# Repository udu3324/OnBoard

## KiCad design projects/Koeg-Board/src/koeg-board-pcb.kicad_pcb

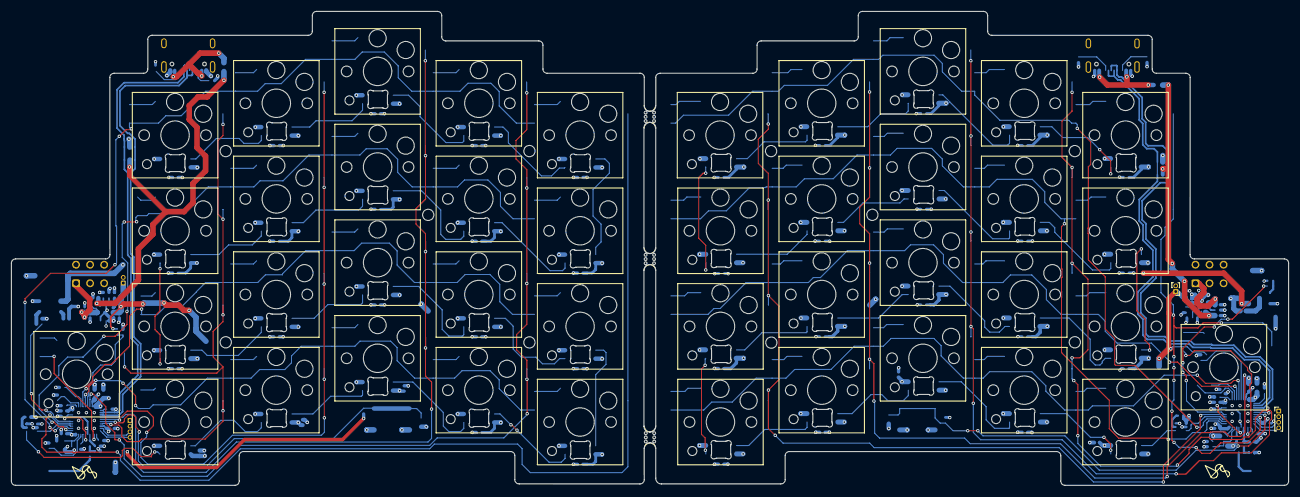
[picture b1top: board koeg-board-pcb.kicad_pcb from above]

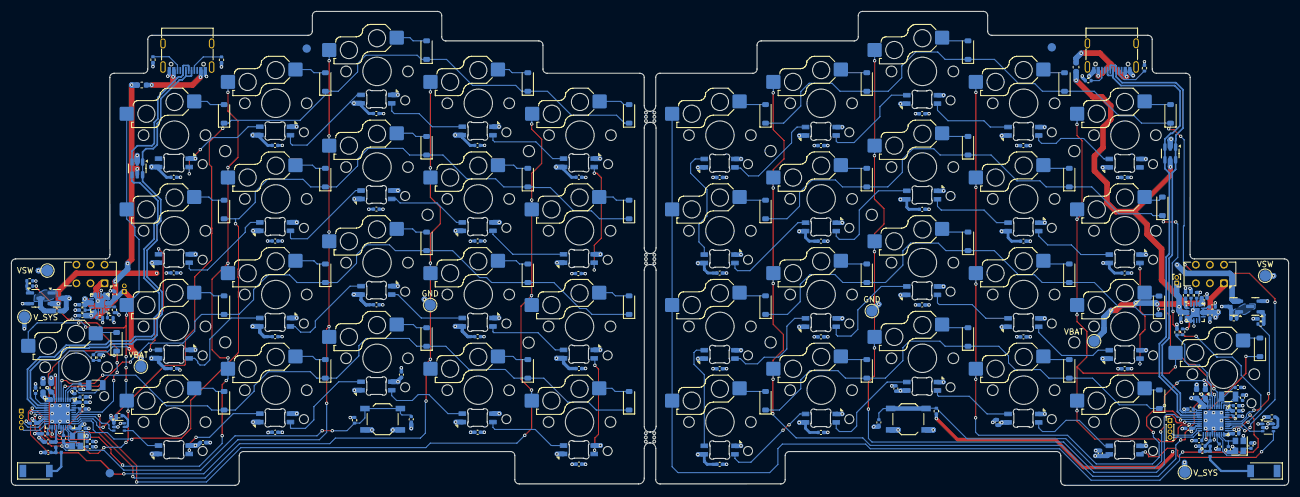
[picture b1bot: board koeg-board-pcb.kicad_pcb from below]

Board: 4 copper layers, 227.1 x 84.3 mm, 290 parts (236 on the bottom side), 175 nets.

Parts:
AE65, AE66: Antenna_Chip; ANTC5020X110N
BO1, BO2, BO3: break off; mouse-bite-2mm-slot
C2, C4, C18, C20, C41, C42, C43, C44, C47, C48, C49, C50, C51, C52, C53, C54, C55, C56, C57, C58, C59, C60, C61, C62, C63, C64, C65, C66, C67, C68, C69, C70, C71, C72, C73, C74, C75, C76, C77, C78, C79, C80, C81, C82, C83, C84, C85, C86: 100nF; C_0402_1005Metric
C5, C21: 100pF; C_0402_1005Metric
C6, C22: 820pF; C_0402_1005Metric
C7, C23, C39, C40: 1uF; C_0402_1005Metric
C9, C25, C87, C88, C89, C90, C91, C92: 4.7uF; C_0402_1005Metric
C10, C19, C24, C26: 4.7uF; C_0603_1608Metric
C11, C12, C15, C16, C27, C28, C31, C32: 12pF; C_0402_1005Metric
C13, C29: 1pF; C_0402_1005Metric
C14, C30: 1.2pF; C_0402_1005Metric
D2, D3, D4, D5, D6, D7, D8, D9, D10, D11, D12, D13, D14, D15, D16, D17, D18, D19, D20, D21, D22, D44, D45, D46, D47, D48, D49, D50, D51, D52, D53, D54, D55, D56, D57, D58, D59, D60, D61, D62, D63, D64: 1N5819; D_SOD-123
D23, D24, D25, D26, D27, D28, D29, D30, D31, D32, D33, D34, D35, D36, D37, D38, D39, D40, D41, D42, D65, D66, D67, D68, D69, D70, D71, D72, D73, D74, D75, D76, D77, D78, D79, D80, D81, D82, D83, D84: SK6812MINI-E; LED_6028R
F1, F2: 500mA; Fuse_0603_1608Metric
FID1, FID2, FID3: Fiducial; Fiducial_1.5mm_Mask3mm
H1, H2, H3, H4, H5, H6, H7, H8, H9, H10: MountingHole; MountingHole_2mm
J1, J4: Conn_01x02; PinHeader_1x02_P1.00mm_Vertical
J2, J5: SWD_Connector; PinHeader_1x04_P1.00mm_Vertical
J3, J6: USB_C_Receptacle_USB2.0_16P; USB_C_Receptacle_G-Switch_GT-USB-7010ASV
L4, L9: 4.7nH; L_0402_1005Metric
L5, L10: 2.2nH; L_0402_1005Metric
LOGO1, LOGO2: Logo_Open_Hardware_Small; BM logo
Q5, Q6: AO3401A; SOT-23
Q7, Q8: 2N7002; SOT-23
R1, R8: 100K; R_0402_1005Metric
R2, R9: 806k; R_0402_1005Metric
R3, R10: 2M; R_0402_1005Metric
R4, R5, R11, R12: 5.1k; R_0402_1005Metric
R6, R7: 100R; R_0402_1005Metric
R13, R14, R16, R18, R20, R22: 10k; R_0402_1005Metric
R27, R28: 3.9k; R_0402_1005Metric
R29, R30, R31, R32, R33, R34: 1.5k; R_0402_1005Metric
SW1, SW24: Reset Button; SW_SPST_TL3342
SW2, SW25: SW_On_Off; SW_CK_JS202011AQN_DPDT_Angled
SW3, SW4, SW5, SW6, SW7, SW8, SW9, SW10, SW11, SW12, SW13, SW14, SW15, SW16, SW17, SW18, SW19, SW20, SW21, SW22, SW26, SW27, SW28, SW29, SW30, SW31, SW32, SW33, SW34, SW35, SW36, SW37, SW38, SW39, SW40, SW41, SW42, SW43, SW44, SW45: SW_Push; SW_Hotswap_Kailh_Choc_V1V2_1.00u
SW23, SW46: SW_Push; SW_Hotswap_Kailh_Choc_V1V2_1.75u_90deg
TP1, TP5: VSW; TestPoint_Pad_D2.0mm
TP2, TP6: V_SYS; TestPoint_Pad_D2.0mm
TP3, TP7: VBAT; TestPoint_Pad_D2.0mm
TP4, TP8: GND; TestPoint_Pad_D2.0mm
U2, U5: USBLC6-2SC6; SOT-23-6
U7, U8: nRF52833_QDxx; QFN-40-1EP_5x5mm_P0.4mm_EP3.6x3.6mm
U9, U10: TXB0101DCK; SOT-363_SC-70-6
U11, U12: BQ24075RGT; VQFN-16-1EP_3x3mm_P0.5mm_EP1.6x1.6mm
Y1, Y2: 32MHz; Crystal_SMD_2520-4Pin_2.5x2.0mm
Y3, Y4: 32.768 kHz; Crystal_SMD_3215-2Pin_3.2x1.5mm

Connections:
/left/ANT: C13.2, L4.1, U7.24 (ANT)
/left/BT_PIN: R2.2, R3.1, U7.6 (P1.09)
/left/CC1: J3.A5 (CC1), R4.1
/left/CC2: J3.B5 (CC2), R5.1
/left/COL0: SW3.2, SW8.2, SW13.2, SW18.2, U7.34 (AIN5/P0.29)
/left/COL1: SW4.2, SW9.2, SW14.2, SW19.2, U7.7 (P0.11)
/left/COL2: SW5.2, SW10.2, SW15.2, SW20.2, U7.14 (P0.15)
/left/COL3: SW6.2, SW11.2, SW16.2, SW21.2, U7.15 (P0.17)
/left/COL4: SW7.2, SW12.2, SW17.2, SW22.2, SW23.2, U7.17 (P0.20)
/left/DEC1: C4.1, U7.1 (DEC1)
/left/DEC3: C5.1, U7.27 (DEC3)
/left/DEC4-6: C7.1, U7.26 (DEC6), U7.38 (DEC4)
/left/DEC5: C6.1, U7.21 (DEC5)
/left/DECUSB: C9.1, U7.11 (DECUSB)
/left/LED_EN: R6.1, U7.35 (AIN6/P0.30)
/left/LED_PIN: U7.33 (AIN4/P0.28), U9.3 (A)
/left/RESET: C2.2, R1.2, SW1.1, U7.16 (P0.18/~RESET)
/left/ROW0: D2.1 (K), D3.1 (K), D4.1 (K), D5.1 (K), D6.1 (K), U7.32 (AIN0/P0.02)
/left/ROW1: D7.1 (K), D8.1 (K), D9.1 (K), D10.1 (K), D11.1 (K), U7.31 (AIN1/P0.03)
/left/ROW2: D12.1 (K), D13.1 (K), D14.1 (K), D15.1 (K), D16.1 (K), U7.4 (AIN2/P0.04)
/left/ROW3: D17.1 (K), D18.1 (K), D19.1 (K), D20.1 (K), D21.1 (K), U7.5 (AIN3/P0.05)
/left/ROW4: D22.1 (K), U7.22 (NFC1/P0.09)
/left/SWDCLK: J2.4, U7.20 (SWDCLK)
/left/SWDIO: J2.3, U7.19 (SWDIO)
/left/USB_D+: J3.A6 (D+), J3.B6 (D+), U2.3 (I/O2), U2.4 (I/O2), U7.13 (D+)
/left/USB_D-: J3.A7 (D-), J3.B7 (D-), U2.1 (I/O1), U2.6 (I/O1), U7.12 (D-)
/left/VBAT: C89.2, J1.1, R2.1, TP3.1, U11.2 (BAT), U11.3 (BAT)
/left/VBUS: C87.2, F1.1, U2.5 (VBUS), U11.13 (IN)
/left/VSW: C19.1, Q5.3 (D), R16.2, SW2.2 (B), TP1.1, U7.9 (VDDH), U7.10 (VBUS), U9.6 (V_{CCB}), U11.6 (EN1)
/left/V_SYS: C10.2, C39.2, C41.2, C43.2, J2.2, R1.1, R20.2, TP2.1, U7.8 (VDD), U7.18 (VDD), U7.30 (VDD), U7.40 (VDD), U9.1 (V_{CCA})
/left/XC1: C11.1, U7.28 (XC1), Y1.1
/left/XC2: C12.1, U7.29 (XC2), Y1.3
/left/XL1: C31.2, U7.2 (XL1/P0.00), Y3.2
/left/XL2: C15.2, U7.3 (XL2/P0.01), Y3.1
/left/leds/DATA: D23.3 (DIN), U9.4 (B)
/left/leds/LED_PWR: C47.2, C49.2, C51.2, C53.2, C55.2, C57.2, C58.2, C59.2, C60.2, C61.2, C67.2, C68.2, C69.2, C70.2, C71.2, C72.2, C73.2, C74.2, C75.2, C76.2, D23.1 (VDD), D24.1 (VDD), D25.1 (VDD), D26.1 (VDD), D27.1 (VDD), D28.1 (VDD), D29.1 (VDD), D30.1 (VDD), D31.1 (VDD), D32.1 (VDD), D33.1 (VDD), D34.1 (VDD), D35.1 (VDD), D36.1 (VDD), D37.1 (VDD), D38.1 (VDD), D39.1 (VDD), D40.1 (VDD), D41.1 (VDD), D42.1 (VDD), Q5.2 (S)
/left/power/ILIM: R29.1, U11.12 (ILIM)
/left/power/ISET: R27.1, U11.16 (ISET)
/left/power/REG-OUT: C91.2, SW2.1 (A), U11.10 (OUT), U11.11 (OUT)
/left/power/TMR: R31.1, U11.14 (TMR)
/left/power/TS: R33.2, U11.1 (TS)
/right/ANT: C29.2, L9.1, U8.24 (ANT)
/right/BT_PIN: R9.2, R10.1, U8.6 (P1.09)
/right/CC1: J6.A5 (CC1), R11.1
/right/CC2: J6.B5 (CC2), R12.1
/right/COL0: SW26.2, SW31.2, SW36.2, SW41.2, U8.34 (AIN5/P0.29)
/right/COL1: SW27.2, SW32.2, SW37.2, SW42.2, U8.7 (P0.11)
/right/COL2: SW28.2, SW33.2, SW38.2, SW43.2, U8.14 (P0.15)
/right/COL3: SW29.2, SW34.2, SW39.2, SW44.2, U8.15 (P0.17)
/right/COL4: SW30.2, SW35.2, SW40.2, SW45.2, SW46.2, U8.17 (P0.20)
/right/DEC1: C20.1, U8.1 (DEC1)
/right/DEC3: C21.1, U8.27 (DEC3)
/right/DEC4-6: C23.1, U8.26 (DEC6), U8.38 (DEC4)
/right/DEC5: C22.1, U8.21 (DEC5)
/right/DECUSB: C25.1, U8.11 (DECUSB)
/right/LED_EN: R7.1, U8.35 (AIN6/P0.30)
/right/LED_PIN: U8.33 (AIN4/P0.28), U10.3 (A)
/right/RESET: C18.2, R8.2, SW24.1, U8.16 (P0.18/~RESET)
/right/ROW0: D44.1 (K), D45.1 (K), D46.1 (K), D47.1 (K), D48.1 (K), U8.32 (AIN0/P0.02)
/right/ROW1: D49.1 (K), D50.1 (K), D51.1 (K), D52.1 (K), D53.1 (K), U8.31 (AIN1/P0.03)
/right/ROW2: D54.1 (K), D55.1 (K), D56.1 (K), D57.1 (K), D58.1 (K), U8.4 (AIN2/P0.04)
/right/ROW3: D59.1 (K), D60.1 (K), D61.1 (K), D62.1 (K), D63.1 (K), U8.5 (AIN3/P0.05)
/right/ROW4: D64.1 (K), U8.22 (NFC1/P0.09)
/right/SWDCLK: J5.4, U8.20 (SWDCLK)
/right/SWDIO: J5.3, U8.19 (SWDIO)
/right/USB_D+: J6.A6 (D+), J6.B6 (D+), U5.3 (I/O2), U5.4 (I/O2), U8.13 (D+)
/right/USB_D-: J6.A7 (D-), J6.B7 (D-), U5.1 (I/O1), U5.6 (I/O1), U8.12 (D-)
/right/VBAT: C90.2, J4.1, R9.1, TP7.1, U12.2 (BAT), U12.3 (BAT)
/right/VBUS: C88.2, F2.1, U5.5 (VBUS), U12.13 (IN)
/right/VSW: C24.1, Q6.3 (D), R18.2, SW25.2 (B), TP5.1, U8.9 (VDDH), U8.10 (VBUS), U10.6 (V_{CCB}), U12.6 (EN1)
/right/V_SYS: C26.2, C40.2, C42.2, C44.2, J5.2, R8.1, R22.2, TP6.1, U8.8 (VDD), U8.18 (VDD), U8.30 (VDD), U8.40 (VDD), U10.1 (V_{CCA})
/right/XC1: C27.1, U8.28 (XC1), Y2.1
/right/XC2: C28.1, U8.29 (XC2), Y2.3
/right/XL1: C32.2, U8.2 (XL1/P0.00), Y4.2
/right/XL2: C16.2, U8.3 (XL2/P0.01), Y4.1
/right/leds/DATA: D65.3 (DIN), U10.4 (B)
/right/leds/LED_PWR: C48.2, C50.2, C52.2, C54.2, C56.2, C62.2, C63.2, C64.2, C65.2, C66.2, C77.2, C78.2, C79.2, C80.2, C81.2, C82.2, C83.2, C84.2, C85.2, C86.2, D65.1 (VDD), D66.1 (VDD), D67.1 (VDD), D68.1 (VDD), D69.1 (VDD), D70.1 (VDD), D71.1 (VDD), D72.1 (VDD), D73.1 (VDD), D74.1 (VDD), D75.1 (VDD), D76.1 (VDD), D77.1 (VDD), D78.1 (VDD), D79.1 (VDD), D80.1 (VDD), D81.1 (VDD), D82.1 (VDD), D83.1 (VDD), D84.1 (VDD), Q6.2 (S)
/right/power/ILIM: R30.1, U12.12 (ILIM)
/right/power/ISET: R28.1, U12.16 (ISET)
/right/power/REG-OUT: C92.2, SW25.1 (A), U12.10 (OUT), U12.11 (OUT)
/right/power/TMR: R32.1, U12.14 (TMR)
/right/power/TS: R34.2, U12.1 (TS)
GND: C2.1, C4.2, C5.2, C6.2, C7.2, C9.2, C10.1, C11.2, C12.2, C13.1, C14.2, C15.1, C16.1, C18.1, C19.2, C20.2, C21.2, C22.2, C23.2, C24.2, C25.2, C26.1, C27.2, C28.2, C29.1, C30.2, C31.1, C32.1, C39.1, C40.1, C41.1, C42.1, C43.1, C44.1, C47.1, C48.1, C49.1, C50.1, C51.1, C52.1, C53.1, C54.1, C55.1, C56.1, C57.1, C58.1, C59.1, C60.1, C61.1, C62.1, C63.1, C64.1, C65.1, C66.1, C67.1, C68.1, C69.1, C70.1, C71.1, C72.1, C73.1, C74.1, C75.1, C76.1, C77.1, C78.1, C79.1, C80.1, C81.1, C82.1, C83.1, C84.1, C85.1, C86.1, C87.1, C88.1, C89.1, C90.1, C91.1, C92.1, D23.4 (VSS), D24.4 (VSS), D25.4 (VSS), D26.4 (VSS), D27.4 (VSS), D28.4 (VSS), D29.4 (VSS), D30.4 (VSS), D31.4 (VSS), D32.4 (VSS), D33.4 (VSS), D34.4 (VSS), D35.4 (VSS), D36.4 (VSS), D37.4 (VSS), D38.4 (VSS), D39.4 (VSS), D40.4 (VSS), D41.4 (VSS), D42.4 (VSS), D65.4 (VSS), D66.4 (VSS), D67.4 (VSS), D68.4 (VSS), D69.4 (VSS), D70.4 (VSS), D71.4 (VSS), D72.4 (VSS), D73.4 (VSS), D74.4 (VSS), D75.4 (VSS), D76.4 (VSS), D77.4 (VSS), D78.4 (VSS), D79.4 (VSS), D80.4 (VSS), D81.4 (VSS), D82.4 (VSS), D83.4 (VSS), D84.4 (VSS), J1.2, J2.1, J3.A1 (GND), J3.A12 (GND), J3.B1 (GND), J3.B12 (GND), J4.2, J5.1, J6.A1 (GND), J6.A12 (GND), J6.B1 (GND), J6.B12 (GND), Q7.2 (S), Q8.2 (S), R3.2, R4.2, R5.2, R10.2, R11.2, R12.2, R13.1, R14.1, R27.2, R28.2, R29.2, R30.2, R31.2, R32.2, R33.1, R34.1, SW1.2, SW24.2, TP4.1, TP8.1, U2.2 (GND), U5.2 (GND), U7.25 (VSS_PA), U7.37 (VSS), U7.41 (VSS), U8.25 (VSS_PA), U8.37 (VSS), U8.41 (VSS), U9.2 (GND), U10.2 (GND), U11.4 (~CE), U11.5 (EN2), U11.8 (VSS), U11.15 (SYSOFF), U11.17 (VSS), U12.4 (~CE), U12.5 (EN2), U12.8 (VSS), U12.15 (SYSOFF), U12.17 (VSS), Y1.2, Y1.4, Y2.2, Y2.4
unnamed: AE65.2 (PCB_Trace), L5.2
unnamed: AE66.2 (PCB_Trace), L10.2
unnamed: C14.1, L4.2, L5.1
unnamed: C30.1, L9.2, L10.1
unnamed: D2.2 (A), SW3.1
unnamed: D3.2 (A), SW4.1
unnamed: D4.2 (A), SW5.1
unnamed: D5.2 (A), SW6.1
unnamed: D6.2 (A), SW7.1
unnamed: D7.2 (A), SW8.1
unnamed: D8.2 (A), SW9.1
unnamed: D9.2 (A), SW10.1
unnamed: D10.2 (A), SW11.1
unnamed: D11.2 (A), SW12.1
unnamed: D12.2 (A), SW13.1
unnamed: D13.2 (A), SW14.1
unnamed: D14.2 (A), SW15.1
unnamed: D15.2 (A), SW16.1
unnamed: D16.2 (A), SW17.1
unnamed: D17.2 (A), SW18.1
unnamed: D18.2 (A), SW19.1
unnamed: D19.2 (A), SW20.1
unnamed: D20.2 (A), SW21.1
unnamed: D21.2 (A), SW22.1
unnamed: D22.2 (A), SW23.1
unnamed: D23.2 (DOUT), D24.3 (DIN)
unnamed: D24.2 (DOUT), D25.3 (DIN)
unnamed: D25.2 (DOUT), D26.3 (DIN)
unnamed: D26.2 (DOUT), D27.3 (DIN)
unnamed: D27.2 (DOUT), D32.3 (DIN)
unnamed: D28.3 (DIN), D29.2 (DOUT)
unnamed: D28.2 (DOUT), D33.3 (DIN)
unnamed: D29.3 (DIN), D30.2 (DOUT)
unnamed: D30.3 (DIN), D31.2 (DOUT)
unnamed: D31.3 (DIN), D32.2 (DOUT)
unnamed: D33.2 (DOUT), D34.3 (DIN)
unnamed: D34.2 (DOUT), D35.3 (DIN)
unnamed: D35.2 (DOUT), D36.3 (DIN)
unnamed: D36.2 (DOUT), D37.3 (DIN)
unnamed: D37.2 (DOUT), D42.3 (DIN)
unnamed: D38.3 (DIN), D39.2 (DOUT)
unnamed: D39.3 (DIN), D40.2 (DOUT)
unnamed: D40.3 (DIN), D41.2 (DOUT)
unnamed: D41.3 (DIN), D42.2 (DOUT)
unnamed: D44.2 (A), SW26.1
unnamed: D45.2 (A), SW27.1
unnamed: D46.2 (A), SW28.1
unnamed: D47.2 (A), SW29.1
unnamed: D48.2 (A), SW30.1
unnamed: D49.2 (A), SW31.1
unnamed: D50.2 (A), SW32.1
unnamed: D51.2 (A), SW33.1
unnamed: D52.2 (A), SW34.1
unnamed: D53.2 (A), SW35.1
unnamed: D54.2 (A), SW36.1
unnamed: D55.2 (A), SW37.1
unnamed: D56.2 (A), SW38.1
unnamed: D57.2 (A), SW39.1
unnamed: D58.2 (A), SW40.1
unnamed: D59.2 (A), SW41.1
unnamed: D60.2 (A), SW42.1
unnamed: D61.2 (A), SW43.1
unnamed: D62.2 (A), SW44.1
unnamed: D63.2 (A), SW45.1
unnamed: D64.2 (A), SW46.1
unnamed: D65.2 (DOUT), D66.3 (DIN)
unnamed: D66.2 (DOUT), D67.3 (DIN)
unnamed: D67.2 (DOUT), D68.3 (DIN)
unnamed: D68.2 (DOUT), D69.3 (DIN)
unnamed: D69.2 (DOUT), D74.3 (DIN)
unnamed: D70.3 (DIN), D71.2 (DOUT)
unnamed: D70.2 (DOUT), D75.3 (DIN)
unnamed: D71.3 (DIN), D72.2 (DOUT)
unnamed: D72.3 (DIN), D73.2 (DOUT)
unnamed: D73.3 (DIN), D74.2 (DOUT)
unnamed: D75.2 (DOUT), D76.3 (DIN)
unnamed: D76.2 (DOUT), D77.3 (DIN)
unnamed: D77.2 (DOUT), D78.3 (DIN)
unnamed: D78.2 (DOUT), D79.3 (DIN)
unnamed: D79.2 (DOUT), D84.3 (DIN)
unnamed: D80.3 (DIN), D81.2 (DOUT)
unnamed: D81.3 (DIN), D82.2 (DOUT)
unnamed: D82.3 (DIN), D83.2 (DOUT)
unnamed: D83.3 (DIN), D84.2 (DOUT)
unnamed: F1.2, J3.A4 (VBUS), J3.A9 (VBUS), J3.B4 (VBUS), J3.B9 (VBUS)
unnamed: F2.2, J6.A4 (VBUS), J6.A9 (VBUS), J6.B4 (VBUS), J6.B9 (VBUS)
unnamed: Q5.1 (G), Q7.3 (D), R16.1
unnamed: Q6.1 (G), Q8.3 (D), R18.1
unnamed: Q7.1 (G), R6.2, R13.2
unnamed: Q8.1 (G), R7.2, R14.2
unnamed: R20.1, U9.5 (OE)
unnamed: R22.1, U10.5 (OE)

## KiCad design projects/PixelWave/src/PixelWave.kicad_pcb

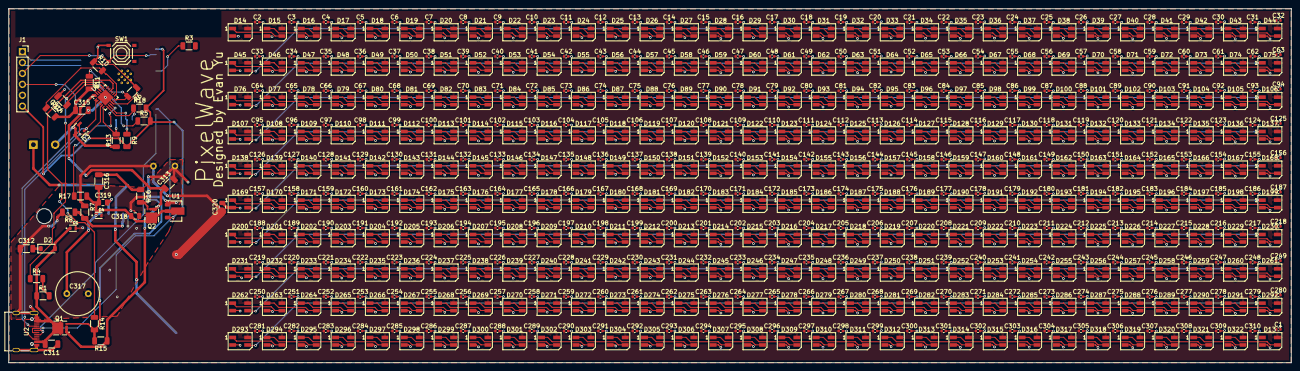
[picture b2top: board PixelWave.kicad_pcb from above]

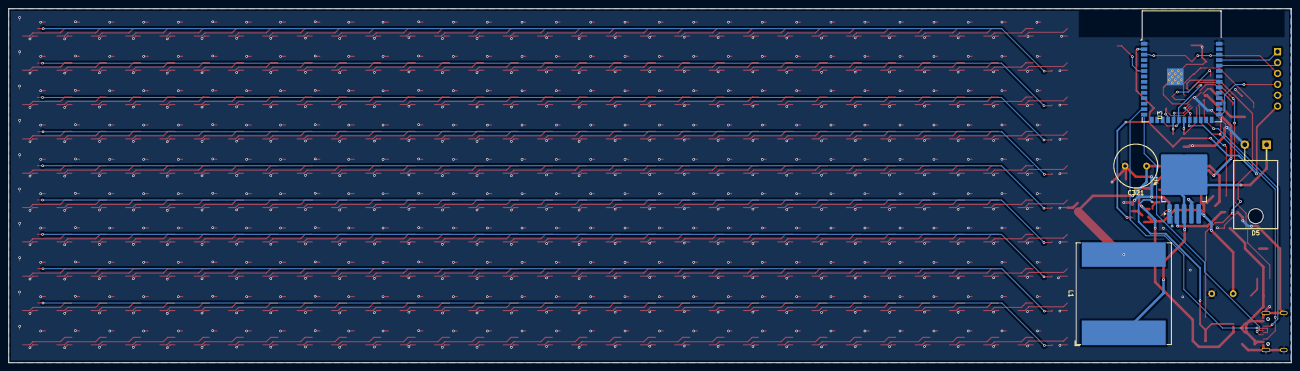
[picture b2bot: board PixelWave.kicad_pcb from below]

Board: 2 copper layers, 298.9 x 82.5 mm, 663 parts (5 on the bottom side), 343 nets.

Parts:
C1, C2, C3, C4, C5, C6, C7, C8, C9, C10, C11, C12, C13, C14, C15, C16, C17, C18, C19, C20, C21, C22, C23, C24, C25, C26, C27, C28, C29, C30, C31, C32, C33, C34, C35, C36, C37, C38, C39, C40, C41, C42, C43, C44, C45, C46, C47, C48, C49, C50, C51, C52, C53, C54, C55, C56, C57, C58, C59, C60, C61, C62, C63, C64, C65, C66, C67, C68, C69, C70, C71, C72, C73, C74, C75, C76, C77, C78, C79, C80, C81, C82, C83, C84, C85, C86, C87, C88, C89, C90, C91, C92, C93, C94, C95, C96, C97, C98, C99, C100, C101, C102, C103, C104, C105, C106, C107, C108, C109, C110, C111, C112, C113, C114, C115, C116, C117, C118, C119, C120, C121, C122, C123, C124, C125, C126, C127, C128, C129, C130, C131, C132, C133, C134, C135, C136, C137, C138, C139, C140, C141, C142, C143, C144, C145, C146, C147, C148, C149, C150, C151, C152, C153, C154, C155, C156, C157, C158, C159, C160, C161, C162, C163, C164, C165, C166, C167, C168, C169, C170, C171, C172, C173, C174, C175, C176, C177, C178, C179, C180, C181, C182, C183, C184, C185, C186, C187, C188, C189, C190, C191, C192, C193, C194, C195, C196, C197, C198, C199, C200, C201, C202, C203, C204, C205, C206, C207, C208, C209, C210, C211, C212, C213, C214, C215, C216, C217, C218, C219, C220, C221, C222, C223, C224, C225, C226, C227, C228, C229, C230, C231, C232, C233, C234, C235, C236, C237, C238, C239, C240, C241, C242, C243, C244, C245, C246, C247, C248, C249, C250, C251, C252, C253, C254, C255, C256, C257, C258, C259, C260, C261, C262, C263, C264, C265, C266, C267, C268, C269, C270, C271, C272, C273, C274, C275, C276, C277, C278, C279, C280, C281, C282, C283, C284, C285, C286, C287, C288, C289, C290, C291, C292, C293, C294, C295, C296, C297, C298, C299, C300, C301, C302, C303, C304, C305, C306, C307, C308, C309, C310: 0.1uF; C_0402_1005Metric
C311: 4.7uF; C_1206_3216Metric
C312, C313, C314, C315: 1uF; C_1206_3216Metric
C316: 100nF; C_1206_3216Metric
C317: 470uF/50V; C_Radial_D10.0mm_H16.0mm_P5.00mm
C318, C319, C320: 1uF; C_0805_2012Metric
C321: 1000uF; C_Radial_D10.0mm_H16.0mm_P5.00mm
D1, D4: ESDA25P35; TVS_ESDA25P35-1U1M
D2: 1N5819W; D_SOD-123
D3: ESDA5V3L; SOT-23-3
D5: MBR1545; TO-220-2_Horizontal_TabDown
D13, D14, D15, D16, D17, D18, D19, D20, D21, D22, D23, D24, D25, D26, D27, D28, D29, D30, D31, D32, D33, D34, D35, D36, D37, D38, D39, D40, D41, D42, D43, D44, D45, D46, D47, D48, D49, D50, D51, D52, D53, D54, D55, D56, D57, D58, D59, D60, D61, D62, D63, D64, D65, D66, D67, D68, D69, D70, D71, D72, D73, D74, D75, D76, D77, D78, D79, D80, D81, D82, D83, D84, D85, D86, D87, D88, D89, D90, D91, D92, D93, D94, D95, D96, D97, D98, D99, D100, D101, D102, D103, D104, D105, D106, D107, D108, D109, D110, D111, D112, D113, D114, D115, D116, D117, D118, D119, D120, D121, D122, D123, D124, D125, D126, D127, D128, D129, D130, D131, D132, D133, D134, D135, D136, D137, D138, D139, D140, D141, D142, D143, D144, D145, D146, D147, D148, D149, D150, D151, D152, D153, D154, D155, D156, D157, D158, D159, D160, D161, D162, D163, D164, D165, D166, D167, D168, D169, D170, D171, D172, D173, D174, D175, D176, D177, D178, D179, D180, D181, D182, D183, D184, D185, D186, D187, D188, D189, D190, D191, D192, D193, D194, D195, D196, D197, D198, D199, D200, D201, D202, D203, D204, D205, D206, D207, D208, D209, D210, D211, D212, D213, D214, D215, D216, D217, D218, D219, D220, D221, D222, D223, D224, D225, D226, D227, D228, D229, D230, D231, D232, D233, D234, D235, D236, D237, D238, D239, D240, D241, D242, D243, D244, D245, D246, D247, D248, D249, D250, D251, D252, D253, D254, D255, D256, D257, D258, D259, D260, D261, D262, D263, D264, D265, D266, D267, D268, D269, D270, D271, D272, D273, D274, D275, D276, D277, D278, D279, D280, D281, D282, D283, D284, D285, D286, D287, D288, D289, D290, D291, D292, D293, D294, D295, D296, D297, D298, D299, D300, D301, D302, D303, D304, D305, D306, D307, D308, D309, D310, D311, D312, D313, D314, D315, D316, D317, D318, D319, D320, D321, D322: SK6812; LED_SK6812MINI_PLCC4_3.5x3.5mm_P1.75mm
J1: Conn_01x06; PinSocket_1x06_P2.54mm_Vertical
L1: 47uH/12A; L_Pulse_PA4349
Q1, Q2: STL6P3LLH6
R1: 470; R_1206_3216Metric
R3: 330; R_1206_3216Metric
R4, R17: 1k; R_1206_3216Metric
R5, R9, R18: 4.7k; R_1206_3216Metric
R6, R10, R15: 100k; R_1206_3216Metric
R7, R13: 10k; R_1206_3216Metric
R8: 3.3k; R_1206_3216Metric
R11, R12: NC; R_1206_3216Metric
R14: 22k; R_1206_3216Metric
R16: 100; R_1206_3216Metric
SW1: SW-SMD_4P-L5.1-W5.1-P3.70-LS6.5-TL_H1.5
U1: HT7533-1; SOT-89-3
U2: USB-C-SMD_G-SWITCH_GT-USB-7010ASV
U3: ESP32-S3-WROOM-1
U4: XL4016; TO-263-5_TabPin3
U5: STUSB4500QTR; QFN-24-1EP_4x4mm_P0.5mm_EP2.7x2.7mm

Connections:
+2V7: C315.1, R11.2, R12.2, U5.23 (VREG_2V7)
+3V3: J1.6, R5.2, R9.2, R18.2, U1.3 (VOUT), U3.2 (3V3)
+5V: C1.1, C2.1, C3.1, C4.1, C5.1, C6.1, C7.1, C8.1, C9.1, C10.1, C11.1, C12.1, C13.1, C14.1, C15.1, C16.1, C17.1, C18.1, C19.1, C20.1, C21.1, C22.1, C23.1, C24.1, C25.1, C26.1, C27.1, C28.1, C29.1, C30.1, C31.1, C32.1, C33.1, C34.1, C35.1, C36.1, C37.1, C38.1, C39.1, C40.1, C41.1, C42.1, C43.1, C44.1, C45.1, C46.1, C47.1, C48.1, C49.1, C50.1, C51.1, C52.1, C53.1, C54.1, C55.1, C56.1, C57.1, C58.1, C59.1, C60.1, C61.1, C62.1, C63.1, C64.1, C65.1, C66.1, C67.1, C68.1, C69.1, C70.1, C71.1, C72.1, C73.1, C74.1, C75.1, C76.1, C77.1, C78.1, C79.1, C80.1, C81.1, C82.1, C83.1, C84.1, C85.1, C86.1, C87.1, C88.1, C89.1, C90.1, C91.1, C92.1, C93.1, C94.1, C95.1, C96.1, C97.1, C98.1, C99.1, C100.1, C101.1, C102.1, C103.1, C104.1, C105.1, C106.1, C107.1, C108.1, C109.1, C110.1, C111.1, C112.1, C113.1, C114.1, C115.1, C116.1, C117.1, C118.1, C119.1, C120.1, C121.1, C122.1, C123.1, C124.1, C125.1, C126.1, C127.1, C128.1, C129.1, C130.1, C131.1, C132.1, C133.1, C134.1, C135.1, C136.1, C137.1, C138.1, C139.1, C140.1, C141.1, C142.1, C143.1, C144.1, C145.1, C146.1, C147.1, C148.1, C149.1, C150.1, C151.1, C152.1, C153.1, C154.1, C155.1, C156.1, C157.1, C158.1, C159.1, C160.1, C161.1, C162.1, C163.1, C164.1, C165.1, C166.1, C167.1, C168.1, C169.1, C170.1, C171.1, C172.1, C173.1, C174.1, C175.1, C176.1, C177.1, C178.1, C179.1, C180.1, C181.1, C182.1, C183.1, C184.1, C185.1, C186.1, C187.1, C188.1, C189.1, C190.1, C191.1, C192.1, C193.1, C194.1, C195.1, C196.1, C197.1, C198.1, C199.1, C200.1, C201.1, C202.1, C203.1, C204.1, C205.1, C206.1, C207.1, C208.1, C209.1, C210.1, C211.1, C212.1, C213.1, C214.1, C215.1, C216.1, C217.1, C218.1, C219.1, C220.1, C221.1, C222.1, C223.1, C224.1, C225.1, C226.1, C227.1, C228.1, C229.1, C230.1, C231.1, C232.1, C233.1, C234.1, C235.1, C236.1, C237.1, C238.1, C239.1, C240.1, C241.1, C242.1, C243.1, C244.1, C245.1, C246.1, C247.1, C248.1, C249.1, C250.1, C251.1, C252.1, C253.1, C254.1, C255.1, C256.1, C257.1, C258.1, C259.1, C260.1, C261.1, C262.1, C263.1, C264.1, C265.1, C266.1, C267.1, C268.1, C269.1, C270.1, C271.1, C272.1, C273.1, C274.1, C275.1, C276.1, C277.1, C278.1, C279.1, C280.1, C281.1, C282.1, C283.1, C284.1, C285.1, C286.1, C287.1, C288.1, C289.1, C290.1, C291.1, C292.1, C293.1, C294.1, C295.1, C296.1, C297.1, C298.1, C299.1, C300.1, C301.1, C302.1, C303.1, C304.1, C305.1, C306.1, C307.1, C308.1, C309.1, C310.1, C320.1, C321.1, D13.4 (VDD), D14.4 (VDD), D15.4 (VDD), D16.4 (VDD), D17.4 (VDD), D18.4 (VDD), D19.4 (VDD), D20.4 (VDD), D21.4 (VDD), D22.4 (VDD), D23.4 (VDD), D24.4 (VDD), D25.4 (VDD), D26.4 (VDD), D27.4 (VDD), D28.4 (VDD), D29.4 (VDD), D30.4 (VDD), D31.4 (VDD), D32.4 (VDD), D33.4 (VDD), D34.4 (VDD), D35.4 (VDD), D36.4 (VDD), D37.4 (VDD), D38.4 (VDD), D39.4 (VDD), D40.4 (VDD), D41.4 (VDD), D42.4 (VDD), D43.4 (VDD), D44.4 (VDD), D45.4 (VDD), D46.4 (VDD), D47.4 (VDD), D48.4 (VDD), D49.4 (VDD), D50.4 (VDD), D51.4 (VDD), D52.4 (VDD), D53.4 (VDD), D54.4 (VDD), D55.4 (VDD), D56.4 (VDD), D57.4 (VDD), D58.4 (VDD), D59.4 (VDD), D60.4 (VDD), D61.4 (VDD), D62.4 (VDD), D63.4 (VDD), D64.4 (VDD), D65.4 (VDD), D66.4 (VDD), D67.4 (VDD), D68.4 (VDD), D69.4 (VDD), D70.4 (VDD), D71.4 (VDD), D72.4 (VDD), D73.4 (VDD), D74.4 (VDD), D75.4 (VDD), D76.4 (VDD), D77.4 (VDD), D78.4 (VDD), D79.4 (VDD), D80.4 (VDD), D81.4 (VDD), D82.4 (VDD), D83.4 (VDD), D84.4 (VDD), D85.4 (VDD), D86.4 (VDD), D87.4 (VDD), D88.4 (VDD), D89.4 (VDD), D90.4 (VDD), D91.4 (VDD), D92.4 (VDD), D93.4 (VDD), D94.4 (VDD), D95.4 (VDD), D96.4 (VDD), D97.4 (VDD), D98.4 (VDD), D99.4 (VDD), D100.4 (VDD), D101.4 (VDD), D102.4 (VDD), D103.4 (VDD), D104.4 (VDD), D105.4 (VDD), D106.4 (VDD), D107.4 (VDD), D108.4 (VDD), D109.4 (VDD), D110.4 (VDD), D111.4 (VDD), D112.4 (VDD), D113.4 (VDD), D114.4 (VDD), D115.4 (VDD), D116.4 (VDD), D117.4 (VDD), D118.4 (VDD), D119.4 (VDD), D120.4 (VDD), D121.4 (VDD), D122.4 (VDD), D123.4 (VDD), D124.4 (VDD), D125.4 (VDD), D126.4 (VDD), D127.4 (VDD), D128.4 (VDD), D129.4 (VDD), D130.4 (VDD), D131.4 (VDD), D132.4 (VDD), D133.4 (VDD), D134.4 (VDD), D135.4 (VDD), D136.4 (VDD), D137.4 (VDD), D138.4 (VDD), D139.4 (VDD), D140.4 (VDD), D141.4 (VDD), D142.4 (VDD), D143.4 (VDD), D144.4 (VDD), D145.4 (VDD), D146.4 (VDD), D147.4 (VDD), D148.4 (VDD), D149.4 (VDD), D150.4 (VDD), D151.4 (VDD), D152.4 (VDD), D153.4 (VDD), D154.4 (VDD), D155.4 (VDD), D156.4 (VDD), D157.4 (VDD), D158.4 (VDD), D159.4 (VDD), D160.4 (VDD), D161.4 (VDD), D162.4 (VDD), D163.4 (VDD), D164.4 (VDD), D165.4 (VDD), D166.4 (VDD), D167.4 (VDD), D168.4 (VDD), D169.4 (VDD), D170.4 (VDD), D171.4 (VDD), D172.4 (VDD), D173.4 (VDD), D174.4 (VDD), D175.4 (VDD), D176.4 (VDD), D177.4 (VDD), D178.4 (VDD), D179.4 (VDD), D180.4 (VDD), D181.4 (VDD), D182.4 (VDD), D183.4 (VDD), D184.4 (VDD)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
/ALERT: R5.1, U3.20 (IO12), U5.19 (ALERT)
/C_Vsnk: C316.2, C317.1, C318.1, C319.1, D4.C, Q2.5, Q2.6, Q2.7, Q2.8, Q2.9, R17.1, U1.2 (VIN), U4.5 (VIN)
/EN: J1.3, SW1.3 (C), U3.3 (EN)
/I2C_SCL: R18.1, U3.18 (IO10), U5.7 (SCL)
/I2C_SDA: R9.1, U3.19 (IO11), U5.8 (SDA)
/IO0: J1.4, U3.27 (IO0)
/LED: R3.1, U3.6 (IO6)
/RESET: R13.1, U3.21 (IO13), U5.6 (RESET)
/RX: J1.2, U3.36 (RXD0)
/TX: J1.1, U3.37 (TXD0)
/USB_DM: U2.A7 (DN1), U2.B7 (DN2), U3.13 (USB_D-)
/USB_DP: U2.A6 (DP1), U2.B6 (DP2), U3.14 (USB_D+)
GND: C1.2, C2.2, C3.2, C4.2, C5.2, C6.2, C7.2, C8.2, C9.2, C10.2, C11.2, C12.2, C13.2, C14.2, C15.2, C16.2, C17.2, C18.2, C19.2, C20.2, C21.2, C22.2, C23.2, C24.2, C25.2, C26.2, C27.2, C28.2, C29.2, C30.2, C31.2, C32.2, C33.2, C34.2, C35.2, C36.2, C37.2, C38.2, C39.2, C40.2, C41.2, C42.2, C43.2, C44.2, C45.2, C46.2, C47.2, C48.2, C49.2, C50.2, C51.2, C52.2, C53.2, C54.2, C55.2, C56.2, C57.2, C58.2, C59.2, C60.2, C61.2, C62.2, C63.2, C64.2, C65.2, C66.2, C67.2, C68.2, C69.2, C70.2, C71.2, C72.2, C73.2, C74.2, C75.2, C76.2, C77.2, C78.2, C79.2, C80.2, C81.2, C82.2, C83.2, C84.2, C85.2, C86.2, C87.2, C88.2, C89.2, C90.2, C91.2, C92.2, C93.2, C94.2, C95.2, C96.2, C97.2, C98.2, C99.2, C100.2, C101.2, C102.2, C103.2, C104.2, C105.2, C106.2, C107.2, C108.2, C109.2, C110.2, C111.2, C112.2, C113.2, C114.2, C115.2, C116.2, C117.2, C118.2, C119.2, C120.2, C121.2, C122.2, C123.2, C124.2, C125.2, C126.2, C127.2, C128.2, C129.2, C130.2, C131.2, C132.2, C133.2, C134.2, C135.2, C136.2, C137.2, C138.2, C139.2, C140.2, C141.2, C142.2, C143.2, C144.2, C145.2, C146.2, C147.2, C148.2, C149.2, C150.2, C151.2, C152.2, C153.2, C154.2, C155.2, C156.2, C157.2, C158.2, C159.2, C160.2, C161.2, C162.2, C163.2, C164.2, C165.2, C166.2, C167.2, C168.2, C169.2, C170.2, C171.2, C172.2, C173.2, C174.2, C175.2, C176.2, C177.2, C178.2, C179.2, C180.2, C181.2, C182.2, C183.2, C184.2, C185.2, C186.2, C187.2, C188.2, C189.2, C190.2, C191.2, C192.2, C193.2, C194.2, C195.2, C196.2, C197.2, C198.2, C199.2, C200.2, C201.2, C202.2, C203.2, C204.2, C205.2, C206.2, C207.2, C208.2, C209.2, C210.2, C211.2, C212.2, C213.2, C214.2, C215.2, C216.2, C217.2, C218.2, C219.2, C220.2, C221.2, C222.2, C223.2, C224.2, C225.2, C226.2, C227.2, C228.2, C229.2, C230.2, C231.2, C232.2, C233.2, C234.2, C235.2, C236.2, C237.2, C238.2, C239.2, C240.2, C241.2, C242.2, C243.2, C244.2, C245.2, C246.2, C247.2, C248.2, C249.2, C250.2, C251.2, C252.2, C253.2, C254.2, C255.2, C256.2, C257.2, C258.2, C259.2, C260.2, C261.2, C262.2, C263.2, C264.2, C265.2, C266.2, C267.2, C268.2, C269.2, C270.2, C271.2, C272.2, C273.2, C274.2, C275.2, C276.2, C277.2, C278.2, C279.2, C280.2, C281.2, C282.2, C283.2, C284.2, C285.2, C286.2, C287.2, C288.2, C289.2, C290.2, C291.2, C292.2, C293.2, C294.2, C295.2, C296.2, C297.2, C298.2, C299.2, C300.2, C301.2, C302.2, C303.2, C304.2, C305.2, C306.2, C307.2, C308.2, C309.2, C310.2, C311.2, C312.1, C313.2, C314.2, C315.2, C317.2, C318.2, C320.2, C321.2, D1.A, D3.3 (A), D4.A, D5.2 (A), D13.2 (VSS), D14.2 (VSS), D15.2 (VSS), D16.2 (VSS), D17.2 (VSS), D18.2 (VSS), D19.2 (VSS), D20.2 (VSS), D21.2 (VSS), D22.2 (VSS), D23.2 (VSS), D24.2 (VSS), D25.2 (VSS), D26.2 (VSS), D27.2 (VSS), D28.2 (VSS), D29.2 (VSS), D30.2 (VSS), D31.2 (VSS), D32.2 (VSS), D33.2 (VSS), D34.2 (VSS), D35.2 (VSS), D36.2 (VSS), D37.2 (VSS), D38.2 (VSS), D39.2 (VSS), D40.2 (VSS), D41.2 (VSS), D42.2 (VSS), D43.2 (VSS), D44.2 (VSS), D45.2 (VSS), D46.2 (VSS), D47.2 (VSS), D48.2 (VSS), D49.2 (VSS), D50.2 (VSS), D51.2 (VSS), D52.2 (VSS), D53.2 (VSS), D54.2 (VSS), D55.2 (VSS), D56.2 (VSS), D57.2 (VSS), D58.2 (VSS), D59.2 (VSS), D60.2 (VSS), D61.2 (VSS), D62.2 (VSS), D63.2 (VSS), D64.2 (VSS), D65.2 (VSS), D66.2 (VSS), D67.2 (VSS), D68.2 (VSS), D69.2 (VSS), D70.2 (VSS), D71.2 (VSS), D72.2 (VSS), D73.2 (VSS), D74.2 (VSS), D75.2 (VSS), D76.2 (VSS), D77.2 (VSS), D78.2 (VSS), D79.2 (VSS), D80.2 (VSS), D81.2 (VSS), D82.2 (VSS), D83.2 (VSS), D84.2 (VSS), D85.2 (VSS), D86.2 (VSS), D87.2 (VSS), D88.2 (VSS), D89.2 (VSS), D90.2 (VSS), D91.2 (VSS), D92.2 (VSS), D93.2 (VSS), D94.2 (VSS), D95.2 (VSS), D96.2 (VSS), D97.2 (VSS), D98.2 (VSS), D99.2 (VSS), D100.2 (VSS), D101.2 (VSS), D102.2 (VSS), D103.2 (VSS), D104.2 (VSS), D105.2 (VSS), D106.2 (VSS), D107.2 (VSS), D108.2 (VSS), D109.2 (VSS), D110.2 (VSS), D111.2 (VSS), D112.2 (VSS), D113.2 (VSS), D114.2 (VSS), D115.2 (VSS), D116.2 (VSS), D117.2 (VSS), D118.2 (VSS), D119.2 (VSS), D120.2 (VSS), D121.2 (VSS), D122.2 (VSS), D123.2 (VSS), D124.2 (VSS), D125.2 (VSS), D126.2 (VSS), D127.2 (VSS), D128.2 (VSS), D129.2 (VSS), D130.2 (VSS), D131.2 (VSS), D132.2 (VSS), D133.2 (VSS), D134.2 (VSS), D135.2 (VSS), D136.2 (VSS), D137.2 (VSS), D138.2 (VSS), D139.2 (VSS), D140.2 (VSS), D141.2 (VSS), D142.2 (VSS), D143.2 (VSS), D144.2 (VSS), D145.2 (VSS), D146.2 (VSS), D147.2 (VSS), D148.2 (VSS), D149.2 (VSS), D150.2 (VSS), D151.2 (VSS), D152.2 (VSS), D153.2 (VSS), D154.2 (VSS), D155.2 (VSS), D156.2 (VSS), D157.2 (VSS), D158.2 (VSS), D159.2 (VSS), D160.2 (VSS), D161.2 (VSS), D162.2 (VSS), D163.2 (VSS), D164.2 (VSS), D165.2 (VSS), D166.2 (VSS), D167.2 (VSS), D168.2 (VSS), D169.2 (VSS), D170.2 (VSS), D171.2 (VSS), D172.2 (VSS), D173.2 (VSS)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
unnamed: C316.1, R16.1
unnamed: C312.2, D2.1 (K)
unnamed: D5.1 (K), L1.1, U4.3 (SW)
unnamed: D13.3 (DIN), D322.1 (DOUT)
unnamed: D14.3 (DIN), R3.2
unnamed: D14.1 (DOUT), D15.3 (DIN)
unnamed: D15.1 (DOUT), D16.3 (DIN)
unnamed: D16.1 (DOUT), D17.3 (DIN)
unnamed: D17.1 (DOUT), D18.3 (DIN)
unnamed: D18.1 (DOUT), D19.3 (DIN)
unnamed: D19.1 (DOUT), D20.3 (DIN)
unnamed: D20.1 (DOUT), D21.3 (DIN)
unnamed: D21.1 (DOUT), D22.3 (DIN)
unnamed: D22.1 (DOUT), D23.3 (DIN)
unnamed: D23.1 (DOUT), D24.3 (DIN)
unnamed: D24.1 (DOUT), D25.3 (DIN)
unnamed: D25.1 (DOUT), D26.3 (DIN)
unnamed: D26.1 (DOUT), D27.3 (DIN)
unnamed: D27.1 (DOUT), D28.3 (DIN)
unnamed: D28.1 (DOUT), D29.3 (DIN)
unnamed: D29.1 (DOUT), D30.3 (DIN)
unnamed: D30.1 (DOUT), D31.3 (DIN)
unnamed: D31.1 (DOUT), D32.3 (DIN)
unnamed: D32.1 (DOUT), D33.3 (DIN)
unnamed: D33.1 (DOUT), D34.3 (DIN)
unnamed: D34.1 (DOUT), D35.3 (DIN)
unnamed: D35.1 (DOUT), D36.3 (DIN)
unnamed: D36.1 (DOUT), D37.3 (DIN)
unnamed: D37.1 (DOUT), D38.3 (DIN)
unnamed: D38.1 (DOUT), D39.3 (DIN)
unnamed: D39.1 (DOUT), D40.3 (DIN)
unnamed: D40.1 (DOUT), D41.3 (DIN)
unnamed: D41.1 (DOUT), D42.3 (DIN)
unnamed: D42.1 (DOUT), D43.3 (DIN)
unnamed: D43.1 (DOUT), D44.3 (DIN)
unnamed: D44.1 (DOUT), D45.3 (DIN)
unnamed: D45.1 (DOUT), D46.3 (DIN)
unnamed: D46.1 (DOUT), D47.3 (DIN)
unnamed: D47.1 (DOUT), D48.3 (DIN)
unnamed: D48.1 (DOUT), D49.3 (DIN)
unnamed: D49.1 (DOUT), D50.3 (DIN)
unnamed: D50.1 (DOUT), D51.3 (DIN)
unnamed: D51.1 (DOUT), D52.3 (DIN)
unnamed: D52.1 (DOUT), D53.3 (DIN)
unnamed: D53.1 (DOUT), D54.3 (DIN)
unnamed: D54.1 (DOUT), D55.3 (DIN)
unnamed: D55.1 (DOUT), D56.3 (DIN)
unnamed: D56.1 (DOUT), D57.3 (DIN)
unnamed: D57.1 (DOUT), D58.3 (DIN)
unnamed: D58.1 (DOUT), D59.3 (DIN)
unnamed: D59.1 (DOUT), D60.3 (DIN)
unnamed: D60.1 (DOUT), D61.3 (DIN)
unnamed: D61.1 (DOUT), D62.3 (DIN)
unnamed: D62.1 (DOUT), D63.3 (DIN)
unnamed: D63.1 (DOUT), D64.3 (DIN)
unnamed: D64.1 (DOUT), D65.3 (DIN)
unnamed: D65.1 (DOUT), D66.3 (DIN)
unnamed: D66.1 (DOUT), D67.3 (DIN)
unnamed: D67.1 (DOUT), D68.3 (DIN)
unnamed: D68.1 (DOUT), D69.3 (DIN)
unnamed: D69.1 (DOUT), D70.3 (DIN)
unnamed: D70.1 (DOUT), D71.3 (DIN)
unnamed: D71.1 (DOUT), D72.3 (DIN)
unnamed: D72.1 (DOUT), D73.3 (DIN)
unnamed: D73.1 (DOUT), D74.3 (DIN)
unnamed: D74.1 (DOUT), D75.3 (DIN)
unnamed: D75.1 (DOUT), D76.3 (DIN)
unnamed: D76.1 (DOUT), D77.3 (DIN)
unnamed: D77.1 (DOUT), D78.3 (DIN)
unnamed: D78.1 (DOUT), D79.3 (DIN)
unnamed: D79.1 (DOUT), D80.3 (DIN)
unnamed: D80.1 (DOUT), D81.3 (DIN)
unnamed: D81.1 (DOUT), D82.3 (DIN)
unnamed: D82.1 (DOUT), D83.3 (DIN)
unnamed: D83.1 (DOUT), D84.3 (DIN)
unnamed: D84.1 (DOUT), D85.3 (DIN)
unnamed: D85.1 (DOUT), D86.3 (DIN)
unnamed: D86.1 (DOUT), D87.3 (DIN)
unnamed: D87.1 (DOUT), D88.3 (DIN)
unnamed: D88.1 (DOUT), D89.3 (DIN)
unnamed: D89.1 (DOUT), D90.3 (DIN)
unnamed: D90.1 (DOUT), D91.3 (DIN)
unnamed: D91.1 (DOUT), D92.3 (DIN)
unnamed: D92.1 (DOUT), D93.3 (DIN)
unnamed: D93.1 (DOUT), D94.3 (DIN)
unnamed: D94.1 (DOUT), D95.3 (DIN)
unnamed: D95.1 (DOUT), D96.3 (DIN)
unnamed: D96.1 (DOUT), D97.3 (DIN)
unnamed: D97.1 (DOUT), D98.3 (DIN)
unnamed: D98.1 (DOUT), D99.3 (DIN)
unnamed: D99.1 (DOUT), D100.3 (DIN)
unnamed: D100.1 (DOUT), D101.3 (DIN)
unnamed: D101.1 (DOUT), D102.3 (DIN)
unnamed: D102.1 (DOUT), D103.3 (DIN)
unnamed: D103.1 (DOUT), D104.3 (DIN)
unnamed: D104.1 (DOUT), D105.3 (DIN)
unnamed: D105.1 (DOUT), D106.3 (DIN)
unnamed: D106.1 (DOUT), D107.3 (DIN)
unnamed: D107.1 (DOUT), D108.3 (DIN)
unnamed: D108.1 (DOUT), D109.3 (DIN)
unnamed: D109.1 (DOUT), D110.3 (DIN)
unnamed: D110.1 (DOUT), D111.3 (DIN)
unnamed: D111.1 (DOUT), D112.3 (DIN)
unnamed: D112.1 (DOUT), D113.3 (DIN)
unnamed: D113.1 (DOUT), D114.3 (DIN)
unnamed: D114.1 (DOUT), D115.3 (DIN)
unnamed: D115.1 (DOUT), D116.3 (DIN)
unnamed: D116.1 (DOUT), D117.3 (DIN)
unnamed: D117.1 (DOUT), D118.3 (DIN)
unnamed: D118.1 (DOUT), D119.3 (DIN)
unnamed: D119.1 (DOUT), D120.3 (DIN)
unnamed: D120.1 (DOUT), D121.3 (DIN)
unnamed: D121.1 (DOUT), D122.3 (DIN)
unnamed: D122.1 (DOUT), D123.3 (DIN)
unnamed: D123.1 (DOUT), D124.3 (DIN)
unnamed: D124.1 (DOUT), D125.3 (DIN)
unnamed: D125.1 (DOUT), D126.3 (DIN)
unnamed: D126.1 (DOUT), D127.3 (DIN)
unnamed: D127.1 (DOUT), D128.3 (DIN)
unnamed: D128.1 (DOUT), D129.3 (DIN)
unnamed: D129.1 (DOUT), D130.3 (DIN)
unnamed: D130.1 (DOUT), D131.3 (DIN)
unnamed: D131.1 (DOUT), D132.3 (DIN)
unnamed: D132.1 (DOUT), D133.3 (DIN)
unnamed: D133.1 (DOUT), D134.3 (DIN)
unnamed: D134.1 (DOUT), D135.3 (DIN)
unnamed: D135.1 (DOUT), D136.3 (DIN)
unnamed: D136.1 (DOUT), D137.3 (DIN)
unnamed: D137.1 (DOUT), D138.3 (DIN)
unnamed: D138.1 (DOUT), D139.3 (DIN)
unnamed: D139.1 (DOUT), D140.3 (DIN)
unnamed: D140.1 (DOUT), D141.3 (DIN)
unnamed: D141.1 (DOUT), D142.3 (DIN)
unnamed: D142.1 (DOUT), D143.3 (DIN)
unnamed: D143.1 (DOUT), D144.3 (DIN)
unnamed: D144.1 (DOUT), D145.3 (DIN)
unnamed: D145.1 (DOUT), D146.3 (DIN)
unnamed: D146.1 (DOUT), D147.3 (DIN)
unnamed: D147.1 (DOUT), D148.3 (DIN)
unnamed: D148.1 (DOUT), D149.3 (DIN)
unnamed: D149.1 (DOUT), D150.3 (DIN)
unnamed: D150.1 (DOUT), D151.3 (DIN)
unnamed: D151.1 (DOUT), D152.3 (DIN)
unnamed: D152.1 (DOUT), D153.3 (DIN)
unnamed: D153.1 (DOUT), D154.3 (DIN)
unnamed: D154.1 (DOUT), D155.3 (DIN)
unnamed: D155.1 (DOUT), D156.3 (DIN)
unnamed: D156.1 (DOUT), D157.3 (DIN)
unnamed: D157.1 (DOUT), D158.3 (DIN)
unnamed: D158.1 (DOUT), D159.3 (DIN)
unnamed: D159.1 (DOUT), D160.3 (DIN)
unnamed: D160.1 (DOUT), D161.3 (DIN)
unnamed: D161.1 (DOUT), D162.3 (DIN)
unnamed: D162.1 (DOUT), D163.3 (DIN)
unnamed: D163.1 (DOUT), D164.3 (DIN)
unnamed: D164.1 (DOUT), D165.3 (DIN)
unnamed: D165.1 (DOUT), D166.3 (DIN)
unnamed: D166.1 (DOUT), D167.3 (DIN)
unnamed: D167.1 (DOUT), D168.3 (DIN)
unnamed: D168.1 (DOUT), D169.3 (DIN)
unnamed: D169.1 (DOUT), D170.3 (DIN)
unnamed: D170.1 (DOUT), D171.3 (DIN)
unnamed: D171.1 (DOUT), D172.3 (DIN)
unnamed: D172.1 (DOUT), D173.3 (DIN)
unnamed: D173.1 (DOUT), D174.3 (DIN)
unnamed: D174.1 (DOUT), D175.3 (DIN)
unnamed: D175.1 (DOUT), D176.3 (DIN)
unnamed: D176.1 (DOUT), D177.3 (DIN)
unnamed: D177.1 (DOUT), D178.3 (DIN)
unnamed: D178.1 (DOUT), D179.3 (DIN)
unnamed: D179.1 (DOUT), D180.3 (DIN)
unnamed: D180.1 (DOUT), D181.3 (DIN)
unnamed: D181.1 (DOUT), D182.3 (DIN)
unnamed: D182.1 (DOUT), D183.3 (DIN)
unnamed: D183.1 (DOUT), D184.3 (DIN)
unnamed: D184.1 (DOUT), D185.3 (DIN)
unnamed: D185.1 (DOUT), D186.3 (DIN)
unnamed: D186.1 (DOUT), D187.3 (DIN)
unnamed: D187.1 (DOUT), D188.3 (DIN)
unnamed: D188.1 (DOUT), D189.3 (DIN)
unnamed: D189.1 (DOUT), D190.3 (DIN)
unnamed: D190.1 (DOUT), D191.3 (DIN)
unnamed: D191.1 (DOUT), D192.3 (DIN)
unnamed: D192.1 (DOUT), D193.3 (DIN)
unnamed: D193.1 (DOUT), D194.3 (DIN)
unnamed: D194.1 (DOUT), D195.3 (DIN)
unnamed: D195.1 (DOUT), D196.3 (DIN)
unnamed: D196.1 (DOUT), D197.3 (DIN)
unnamed: D197.1 (DOUT), D198.3 (DIN)
unnamed: D198.1 (DOUT), D199.3 (DIN)
unnamed: D199.1 (DOUT), D200.3 (DIN)
unnamed: D200.1 (DOUT), D201.3 (DIN)
unnamed: D201.1 (DOUT), D202.3 (DIN)
unnamed: D202.1 (DOUT), D203.3 (DIN)
unnamed: D203.1 (DOUT), D204.3 (DIN)
unnamed: D204.1 (DOUT), D205.3 (DIN)
unnamed: D205.1 (DOUT), D206.3 (DIN)
unnamed: D206.1 (DOUT), D207.3 (DIN)
unnamed: D207.1 (DOUT), D208.3 (DIN)
unnamed: D208.1 (DOUT), D209.3 (DIN)
unnamed: D209.1 (DOUT), D210.3 (DIN)
unnamed: D210.1 (DOUT), D211.3 (DIN)
unnamed: D211.1 (DOUT), D212.3 (DIN)
unnamed: D212.1 (DOUT), D213.3 (DIN)
unnamed: D213.1 (DOUT), D214.3 (DIN)
unnamed: D214.1 (DOUT), D215.3 (DIN)
unnamed: D215.1 (DOUT), D216.3 (DIN)
unnamed: D216.1 (DOUT), D217.3 (DIN)
unnamed: D217.1 (DOUT), D218.3 (DIN)
unnamed: D218.1 (DOUT), D219.3 (DIN)
unnamed: D219.1 (DOUT), D220.3 (DIN)
unnamed: D220.1 (DOUT), D221.3 (DIN)
unnamed: D221.1 (DOUT), D222.3 (DIN)
unnamed: D222.1 (DOUT), D223.3 (DIN)
unnamed: D223.1 (DOUT), D224.3 (DIN)
unnamed: D224.1 (DOUT), D225.3 (DIN)
unnamed: D225.1 (DOUT), D226.3 (DIN)
unnamed: D226.1 (DOUT), D227.3 (DIN)
unnamed: D227.1 (DOUT), D228.3 (DIN)
unnamed: D228.1 (DOUT), D229.3 (DIN)
unnamed: D229.1 (DOUT), D230.3 (DIN)
unnamed: D230.1 (DOUT), D231.3 (DIN)
unnamed: D231.1 (DOUT), D232.3 (DIN)
unnamed: D232.1 (DOUT), D233.3 (DIN)
unnamed: D233.1 (DOUT), D234.3 (DIN)
unnamed: D234.1 (DOUT), D235.3 (DIN)
unnamed: D235.1 (DOUT), D236.3 (DIN)
unnamed: D236.1 (DOUT), D237.3 (DIN)
unnamed: D237.1 (DOUT), D238.3 (DIN)
unnamed: D238.1 (DOUT), D239.3 (DIN)
unnamed: D239.1 (DOUT), D240.3 (DIN)
unnamed: D240.1 (DOUT), D241.3 (DIN)
unnamed: D241.1 (DOUT), D242.3 (DIN)
unnamed: D242.1 (DOUT), D243.3 (DIN)
unnamed: D243.1 (DOUT), D244.3 (DIN)
unnamed: D244.1 (DOUT), D245.3 (DIN)
unnamed: D245.1 (DOUT), D246.3 (DIN)
unnamed: D246.1 (DOUT), D247.3 (DIN)
unnamed: D247.1 (DOUT), D248.3 (DIN)
unnamed: D248.1 (DOUT), D249.3 (DIN)
unnamed: D249.1 (DOUT), D250.3 (DIN)
unnamed: D250.1 (DOUT), D251.3 (DIN)
unnamed: D251.1 (DOUT), D252.3 (DIN)
unnamed: D252.1 (DOUT), D253.3 (DIN)
unnamed: D253.1 (DOUT), D254.3 (DIN)
unnamed: D254.1 (DOUT), D255.3 (DIN)
unnamed: D255.1 (DOUT), D256.3 (DIN)
unnamed: D256.1 (DOUT), D257.3 (DIN)
unnamed: D257.1 (DOUT), D258.3 (DIN)
unnamed: D258.1 (DOUT), D259.3 (DIN)
unnamed: D259.1 (DOUT), D260.3 (DIN)
unnamed: D260.1 (DOUT), D261.3 (DIN)
unnamed: D261.1 (DOUT), D262.3 (DIN)
unnamed: D262.1 (DOUT), D263.3 (DIN)
unnamed: D263.1 (DOUT), D264.3 (DIN)
unnamed: D264.1 (DOUT), D265.3 (DIN)
unnamed: D265.1 (DOUT), D266.3 (DIN)
unnamed: D266.1 (DOUT), D267.3 (DIN)
unnamed: D267.1 (DOUT), D268.3 (DIN)
unnamed: D268.1 (DOUT), D269.3 (DIN)
unnamed: D269.1 (DOUT), D270.3 (DIN)
unnamed: D270.1 (DOUT), D271.3 (DIN)
unnamed: D271.1 (DOUT), D272.3 (DIN)
unnamed: D272.1 (DOUT), D273.3 (DIN)
unnamed: D273.1 (DOUT), D274.3 (DIN)
unnamed: D274.1 (DOUT), D275.3 (DIN)
unnamed: D275.1 (DOUT), D276.3 (DIN)
unnamed: D276.1 (DOUT), D277.3 (DIN)
unnamed: D277.1 (DOUT), D278.3 (DIN)
unnamed: D278.1 (DOUT), D279.3 (DIN)
unnamed: D279.1 (DOUT), D280.3 (DIN)
unnamed: D280.1 (DOUT), D281.3 (DIN)
unnamed: D281.1 (DOUT), D282.3 (DIN)
unnamed: D282.1 (DOUT), D283.3 (DIN)
unnamed: D283.1 (DOUT), D284.3 (DIN)
unnamed: D284.1 (DOUT), D285.3 (DIN)
unnamed: D285.1 (DOUT), D286.3 (DIN)
unnamed: D286.1 (DOUT), D287.3 (DIN)
unnamed: D287.1 (DOUT), D288.3 (DIN)
unnamed: D288.1 (DOUT), D289.3 (DIN)
unnamed: D289.1 (DOUT), D290.3 (DIN)
unnamed: D290.1 (DOUT), D291.3 (DIN)
unnamed: D291.1 (DOUT), D292.3 (DIN)
unnamed: D292.1 (DOUT), D293.3 (DIN)
unnamed: D293.1 (DOUT), D294.3 (DIN)
unnamed: D294.1 (DOUT), D295.3 (DIN)
unnamed: D295.1 (DOUT), D296.3 (DIN)
unnamed: D296.1 (DOUT), D297.3 (DIN)
unnamed: D297.1 (DOUT), D298.3 (DIN)
unnamed: D298.1 (DOUT), D299.3 (DIN)
unnamed: D299.1 (DOUT), D300.3 (DIN)
unnamed: D300.1 (DOUT), D301.3 (DIN)
unnamed: D301.1 (DOUT), D302.3 (DIN)
unnamed: D302.1 (DOUT), D303.3 (DIN)
unnamed: D303.1 (DOUT), D304.3 (DIN)
unnamed: D304.1 (DOUT), D305.3 (DIN)
unnamed: D305.1 (DOUT), D306.3 (DIN)
unnamed: D306.1 (DOUT), D307.3 (DIN)
unnamed: D307.1 (DOUT), D308.3 (DIN)
unnamed: D308.1 (DOUT), D309.3 (DIN)
unnamed: D309.1 (DOUT), D310.3 (DIN)
unnamed: D310.1 (DOUT), D311.3 (DIN)
unnamed: D311.1 (DOUT), D312.3 (DIN)
unnamed: D312.1 (DOUT), D313.3 (DIN)
unnamed: D313.1 (DOUT), D314.3 (DIN)
unnamed: D314.1 (DOUT), D315.3 (DIN)
unnamed: D315.1 (DOUT), D316.3 (DIN)
unnamed: D316.1 (DOUT), D317.3 (DIN)
unnamed: D317.1 (DOUT), D318.3 (DIN)
unnamed: D318.1 (DOUT), D319.3 (DIN)
unnamed: D319.1 (DOUT), D320.3 (DIN)
unnamed: D320.1 (DOUT), D321.3 (DIN)
unnamed: D321.1 (DOUT), D322.3 (DIN)
unnamed: Q1.4, Q2.4, R14.2, R15.1, R16.2
unnamed: R1.2, R4.1
unnamed: D3.1 (K), U2.A5 (CC1), U5.1 (CC1DB), U5.2 (CC1)
unnamed: D3.2 (K), U2.B5 (CC2), U5.4 (CC2), U5.5 (CC2DB)
unnamed: R7.2, R8.1, U4.2 (FB)
unnamed: C319.2, U4.4 (VC)
unnamed: R6.2, R11.1, U5.12 (ADDR0)
unnamed: R10.2, R12.1, U5.13 (ADDR1)
unnamed: R17.2, U5.9 (DISCH)
unnamed: R14.1, U5.16 (VBUS_EN_SNK)
unnamed: R4.2, U5.18 (VBUS_VS_DISCH)
unnamed: C313.1, Q1.1, Q1.2, Q1.3, Q2.1, Q2.2, Q2.3, R15.2, U5.24 (VDD)
unnamed: C314.1, U5.21 (VREG_1V2)
VBUS: C311.1, D1.C, D2.2 (A), Q1.5, Q1.6, Q1.7, Q1.8, Q1.9, R1.1, U2.A4B9 (VBUS), U2.B4A9 (VBUS)

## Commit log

2026-03-30 gift tag blog
